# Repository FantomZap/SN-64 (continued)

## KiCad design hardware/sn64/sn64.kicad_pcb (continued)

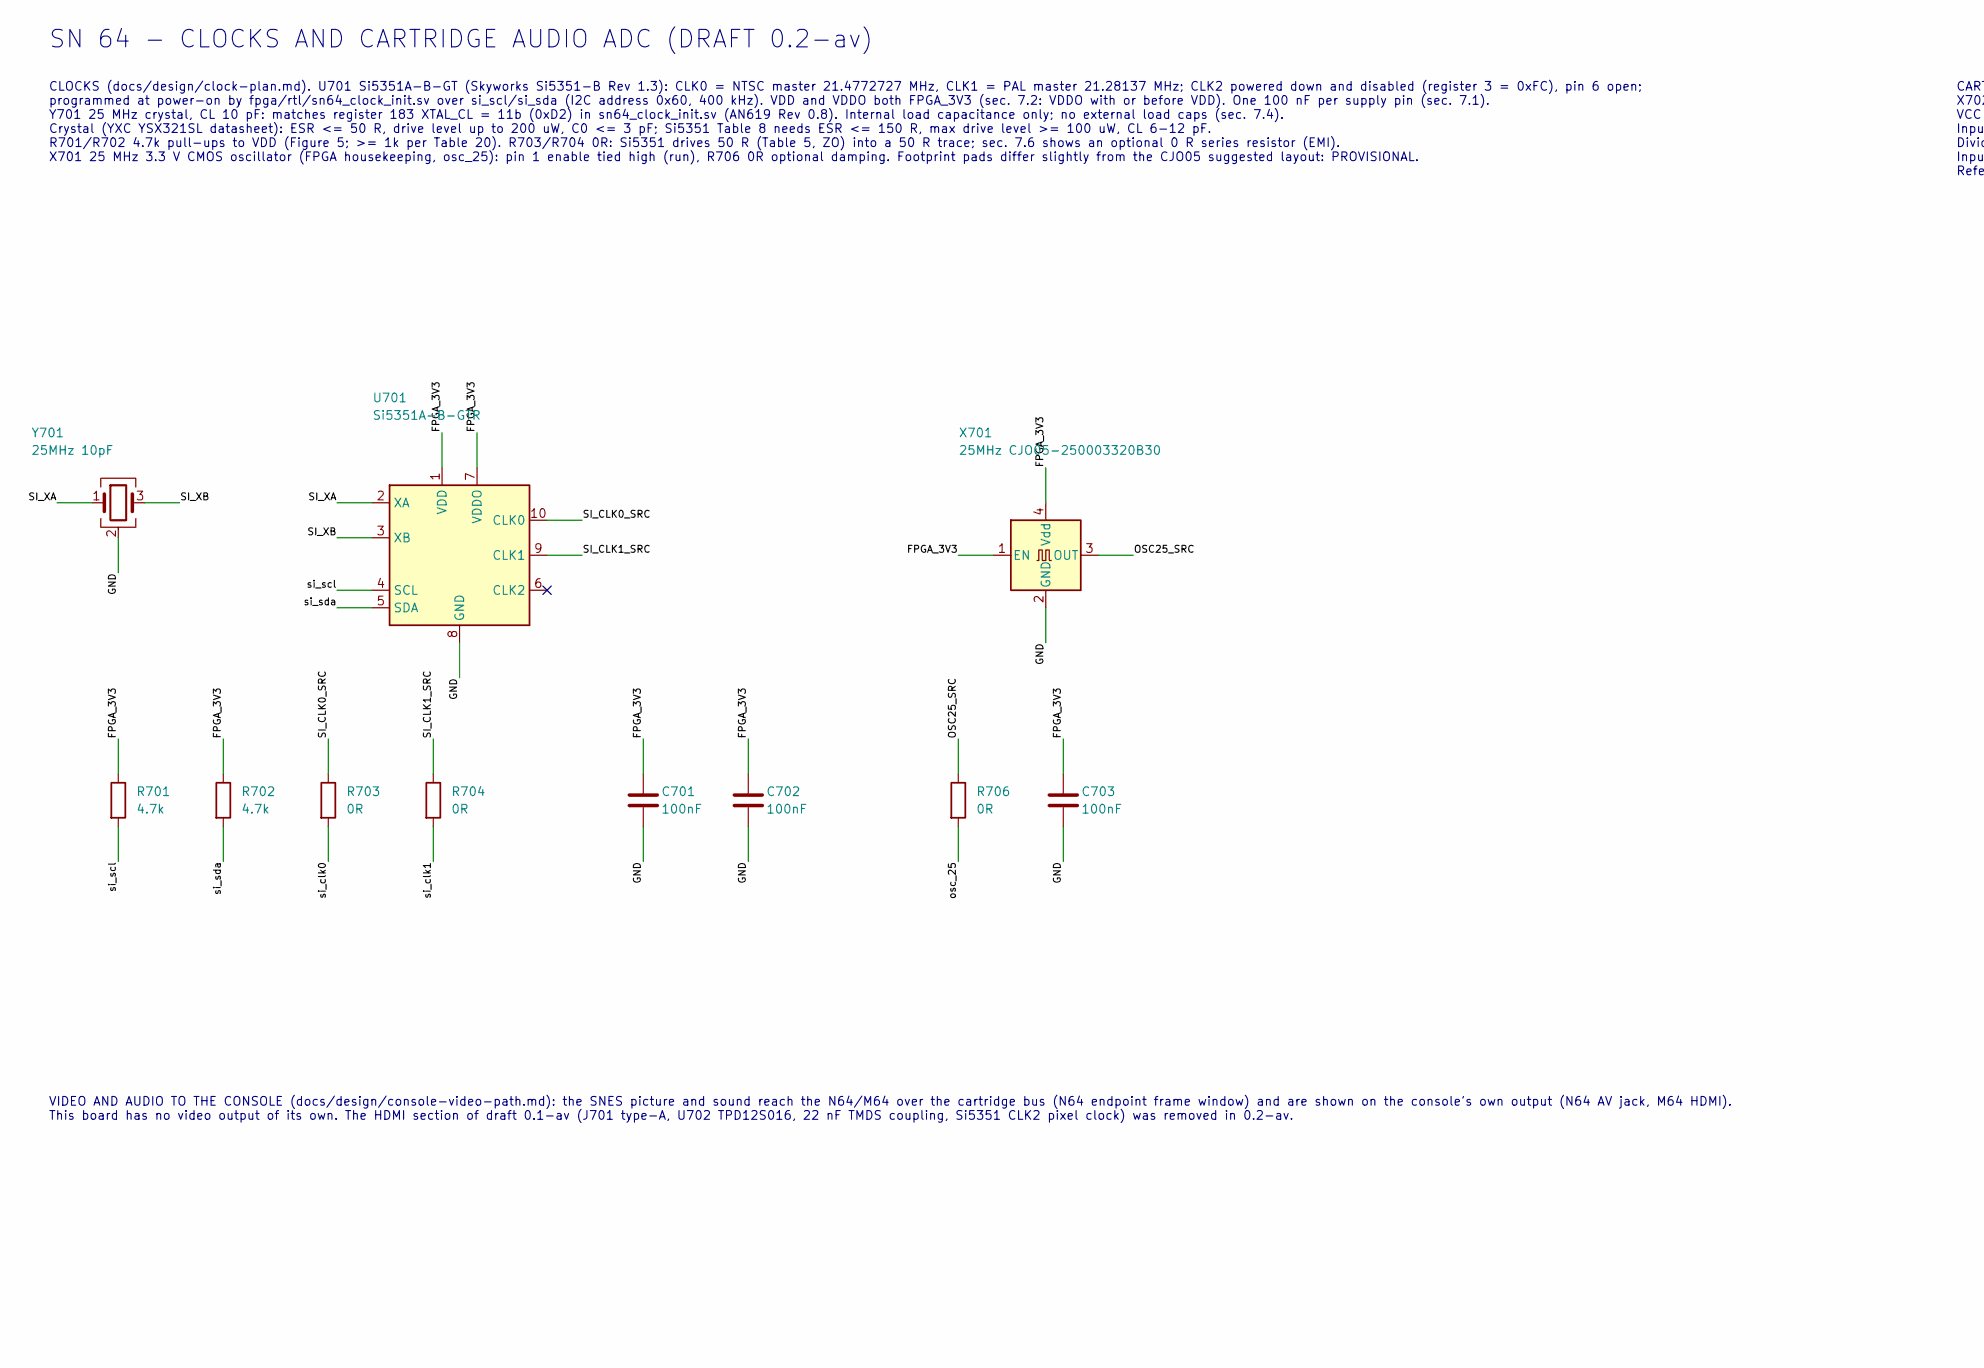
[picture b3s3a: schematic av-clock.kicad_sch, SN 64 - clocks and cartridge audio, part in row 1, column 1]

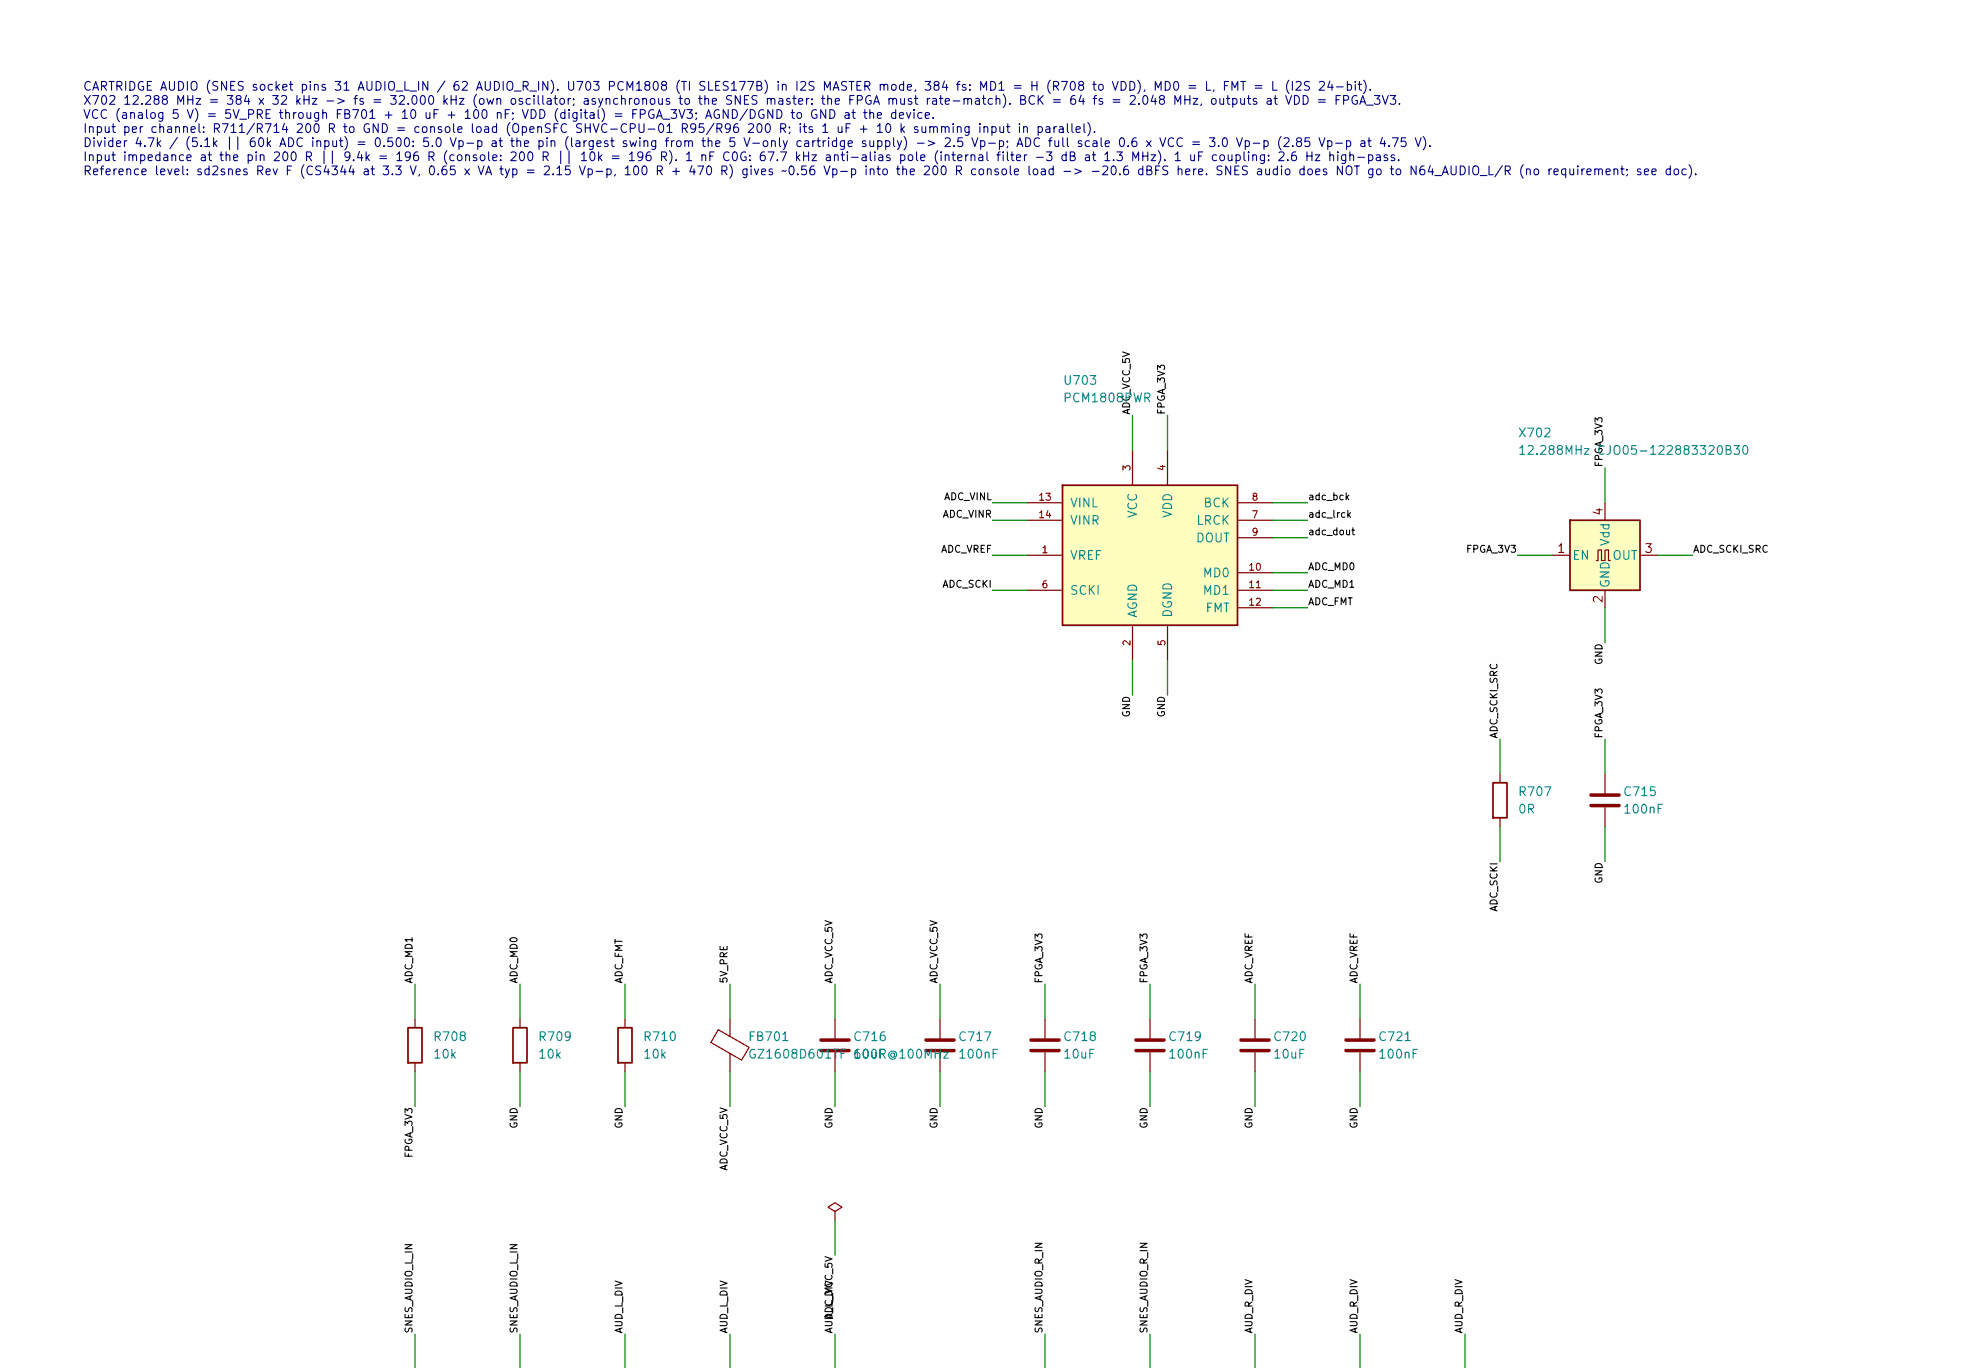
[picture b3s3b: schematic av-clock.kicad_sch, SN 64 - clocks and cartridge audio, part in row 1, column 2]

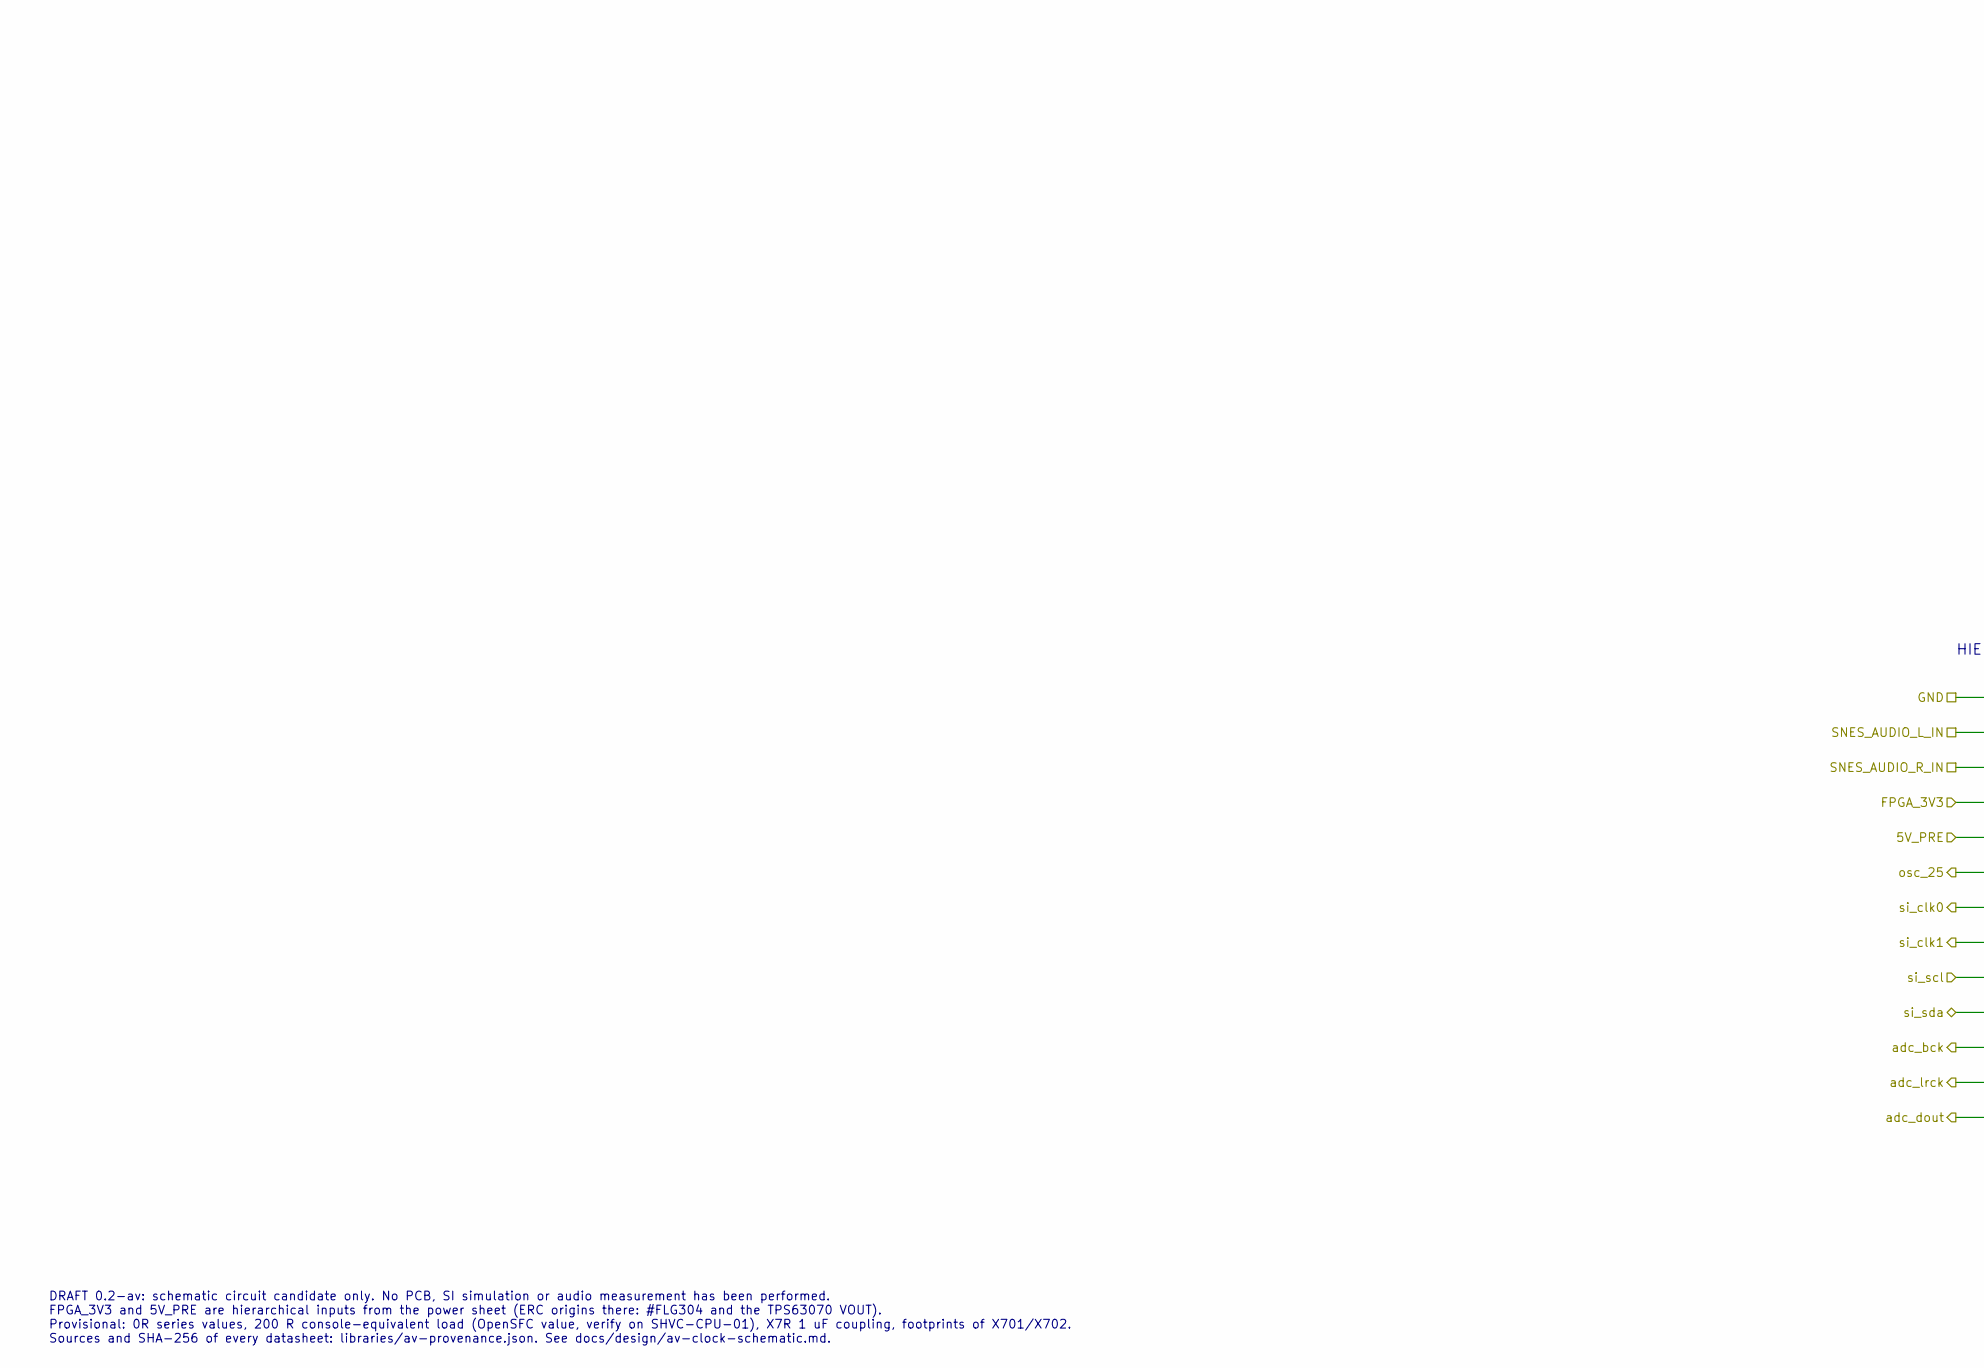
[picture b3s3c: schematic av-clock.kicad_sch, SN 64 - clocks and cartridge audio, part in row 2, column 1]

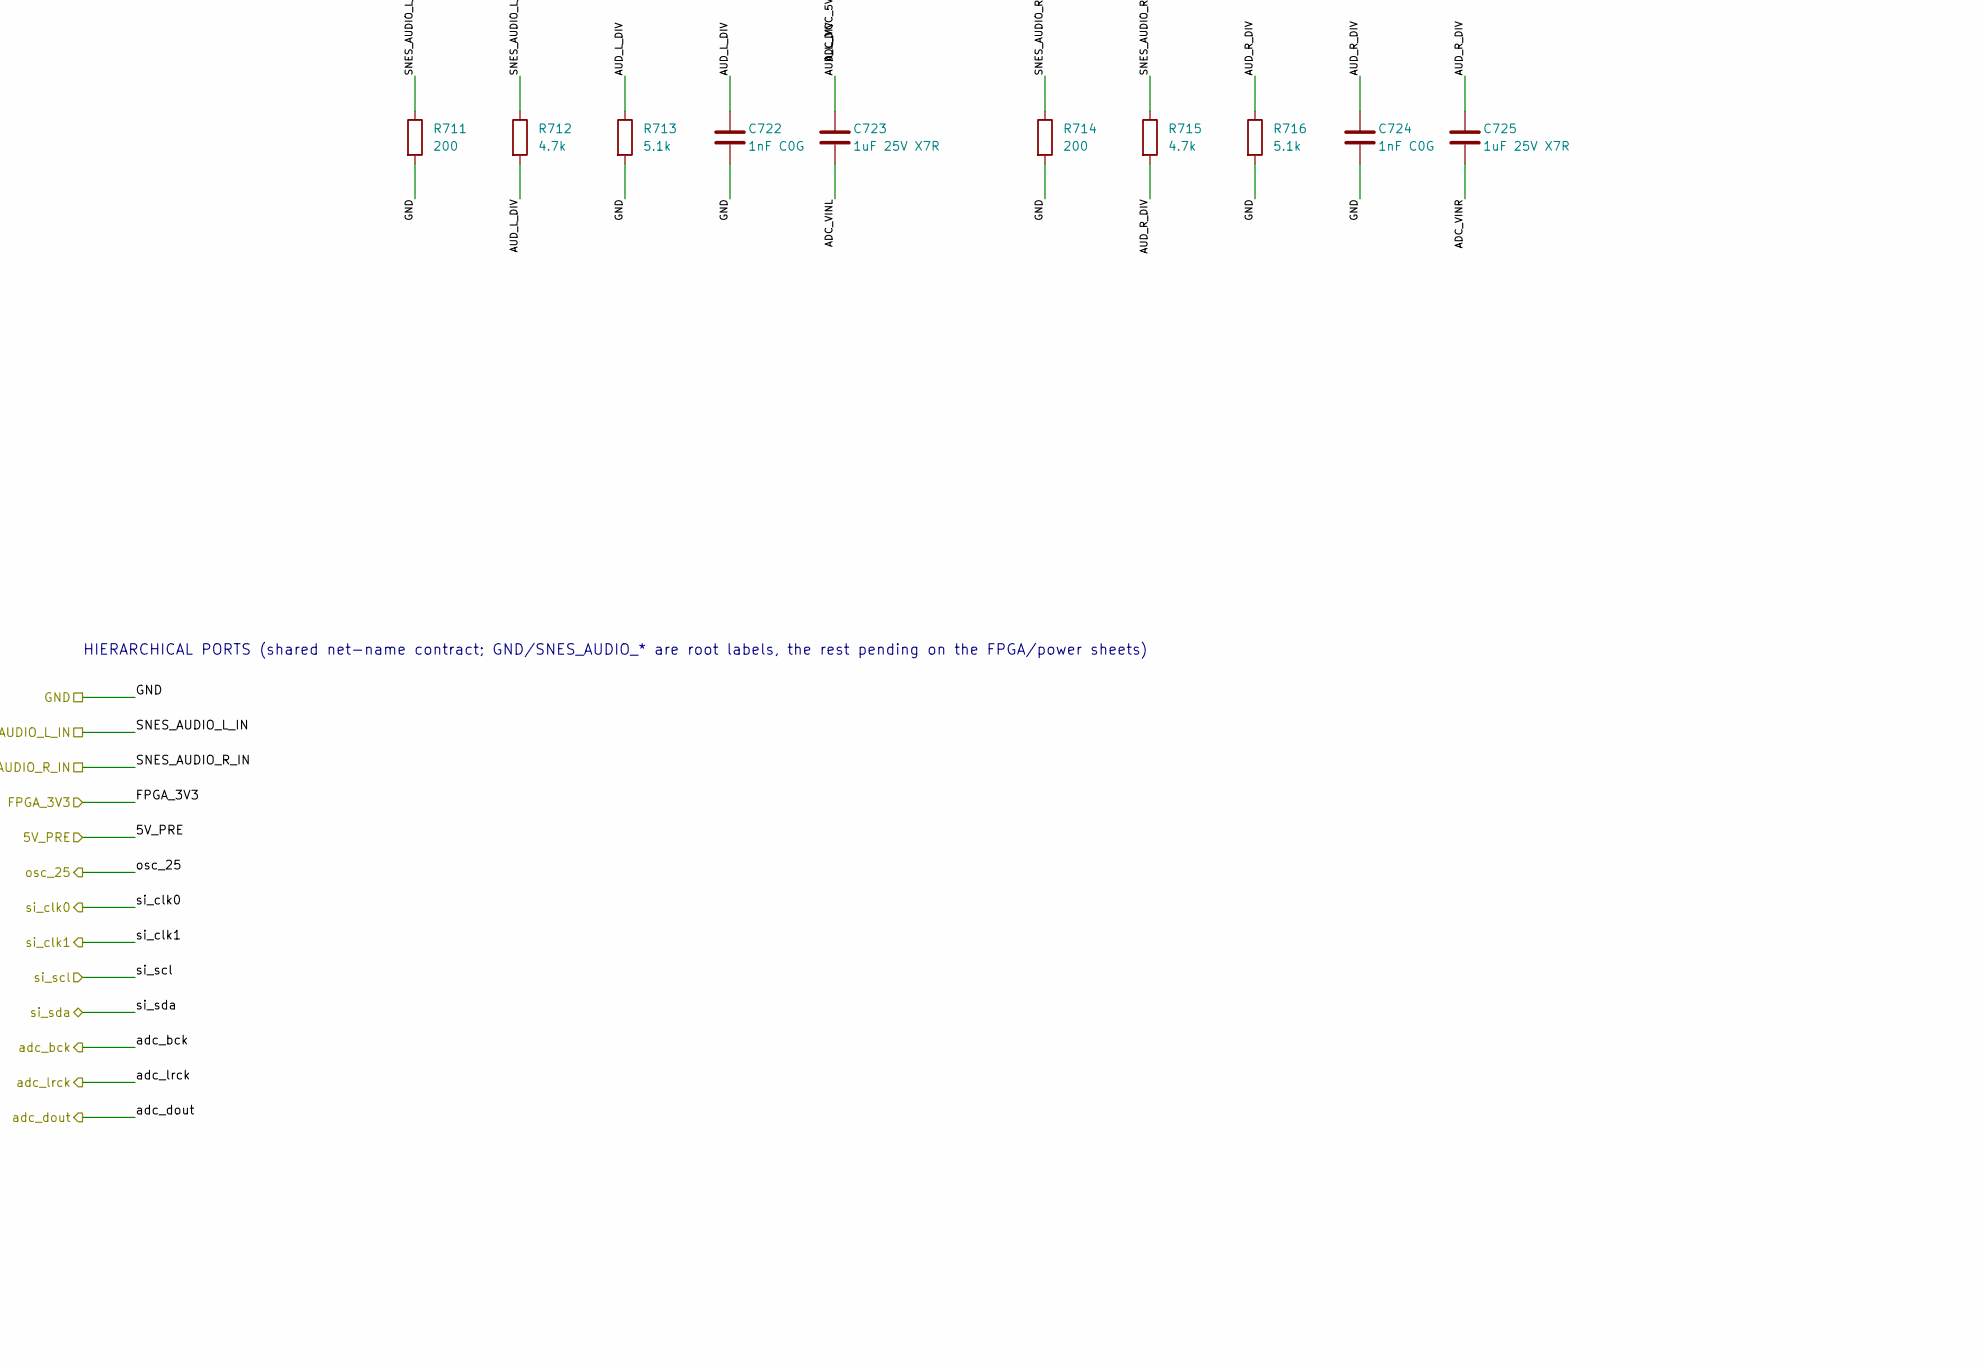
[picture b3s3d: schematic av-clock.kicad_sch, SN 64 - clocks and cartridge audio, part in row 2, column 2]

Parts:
C701, C702, C703, C715, C717, C719, C721: 100nF; C_0603_1608Metric
C716, C718, C720: 10uF; C_0805_2012Metric
C722, C724: 1nF C0G; C_0603_1608Metric
C723, C725: 1uF 25V X7R; C_0805_2012Metric
FB701: GZ1608D601TF 600R@100MHz; L_0603_1608Metric; MPN GZ1608D601TF; LCSC C1002
R701, R702, R712, R715: 4.7k; R_0603_1608Metric
R703, R704, R706, R707: 0R; R_0603_1608Metric
R708, R709, R710: 10k; R_0603_1608Metric
R711, R714: 200; R_0603_1608Metric
R713, R716: 5.1k; R_0603_1608Metric
U701: Si5351A-B-GTR; MSOP-10_3x3mm_P0.5mm; MPN Si5351A-B-GTR; LCSC C504891
U703: PCM1808PWR; TSSOP-14_4.4x5mm_P0.65mm; MPN PCM1808PWR; LCSC C55513
X701: 25MHz CJO05-250003320B30; Oscillator_SMD_Abracon_ASE-4Pin_3.2x2.5mm; MPN CJO05-250003320B30; LCSC C712741
X702: 12.288MHz CJO05-122883320B30; Oscillator_SMD_Abracon_ASE-4Pin_3.2x2.5mm; MPN CJO05-122883320B30; LCSC C712747
Y701: 25MHz 10pF; Crystal_SMD_3225-4Pin_3.2x2.5mm; MPN X322525MMB4SI; LCSC C70582

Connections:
/5V_PRE: FB701.1; also elsewhere on the board
/AV clock and cartridge audio/ADC_FMT: R710.1, U703.12 (FMT)
/AV clock and cartridge audio/ADC_MD0: R709.1, U703.10 (MD0)
/AV clock and cartridge audio/ADC_MD1: R708.1, U703.11 (MD1)
/AV clock and cartridge audio/ADC_SCKI: R707.2, U703.6 (SCKI)
/AV clock and cartridge audio/ADC_SCKI_SRC: R707.1, X702.3 (OUT)
/AV clock and cartridge audio/ADC_VCC_5V: C716.1, C717.1, FB701.2, U703.3 (VCC)
/AV clock and cartridge audio/ADC_VINL: C723.2, U703.13 (VINL)
/AV clock and cartridge audio/ADC_VINR: C725.2, U703.14 (VINR)
/AV clock and cartridge audio/ADC_VREF: C720.1, C721.1, U703.1 (VREF)
/AV clock and cartridge audio/AUD_L_DIV: C722.1, C723.1, R712.2, R713.1
/AV clock and cartridge audio/AUD_R_DIV: C724.1, C725.1, R715.2, R716.1
/AV clock and cartridge audio/OSC25_SRC: R706.1, X701.3 (OUT)
/AV clock and cartridge audio/SI_CLK0_SRC: R703.1, U701.10 (CLK0)
/AV clock and cartridge audio/SI_CLK1_SRC: R704.1, U701.9 (CLK1)
/AV clock and cartridge audio/SI_XA: U701.2 (XA), Y701.1
/AV clock and cartridge audio/SI_XB: U701.3 (XB), Y701.3
/FPGA_3V3: C701.1, C702.1, C703.1, C715.1, C718.1, C719.1, R701.1, R702.1, R708.2, U701.1 (VDD), U701.7 (VDDO), U703.4 (VDD), X701.1 (EN), X701.4 (Vdd), X702.1 (EN), X702.4 (Vdd); also elsewhere on the board
/GND: C701.2, C702.2, C703.2, C715.2, C716.2, C717.2, C718.2, C719.2, C720.2, C721.2, C722.2, C724.2, R709.2, R710.2, R711.2, R713.2, R714.2, R716.2, U701.8 (GND), U703.2 (AGND), U703.5 (DGND), X701.2 (GND), X702.2 (GND), Y701.2 (G), Y701.4 (G); also elsewhere on the board
/SNES_AUDIO_L_IN: R711.1, R712.1; also elsewhere on the board
/SNES_AUDIO_R_IN: R714.1, R715.1; also elsewhere on the board
/adc_bck: U703.8 (BCK); also elsewhere on the board
/adc_dout: U703.9 (DOUT); also elsewhere on the board
/adc_lrck: U703.7 (LRCK); also elsewhere on the board
/osc_25: R706.2; also elsewhere on the board
/si_clk0: R703.2; also elsewhere on the board
/si_clk1: R704.2; also elsewhere on the board
/si_scl: R701.2, U701.4 (SCL); also elsewhere on the board
/si_sda: R702.2, U701.5 (SDA); also elsewhere on the board

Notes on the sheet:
SN 64 - CLOCKS AND CARTRIDGE AUDIO ADC (DRAFT 0.2-av)
CLOCKS (docs/design/clock-plan.md). U701 Si5351A-B-GT (Skyworks Si5351-B Rev 1.3): CLK0 = NTSC master 21.4772727 MHz, CLK1 = PAL master 21.28137 MHz; CLK2 powered down and disabled (register 3 = 0xFC), pin 6 open; programmed at power-on by fpga/rtl/sn64_clock_init.sv over si_scl/si_sda (I2C address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
VIDEO AND AUDIO TO THE CONSOLE (docs/design/console-video-path.md): the SNES picture and sound reach the N64/M64 over the cartridge bus (N64 endpoint frame window) and are shown on the console's own output (N64 AV jack, M64 HDMI). This board has no video output of its own. The HDMI section of draft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
CARTRIDGE AUDIO (SNES socket pins 31 AUDIO_L_IN / 62 AUDIO_R_IN). U703 PCM1808 (TI SLES177B) in I2S MASTER mode, 384 fs: MD1 = H (R708 to VDD), MD0 = L, FMT = L (I2S 24-bit). X702 12.288 MHz = 384 x 32 kHz -> fs = 32.000 kHz (own oscillator; asynchronous to the SNES master: the FPGA must rate-match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
HIERARCHICAL PORTS (shared net-name contract; GND/SNES_AUDIO_* are root labels, the rest pending on the FPGA/power sheets)
DRAFT 0.2-av: schematic circuit candidate only. No PCB, SI simulation or audio measurement has been performed. FPGA_3V3 and 5V_PRE are hierarchical inputs from the power sheet (ERC origins there: #FLG304 and the TPS63070 VOUT). Provisional: 0R series values, 200 R console-equivalent load (OpenSFC v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

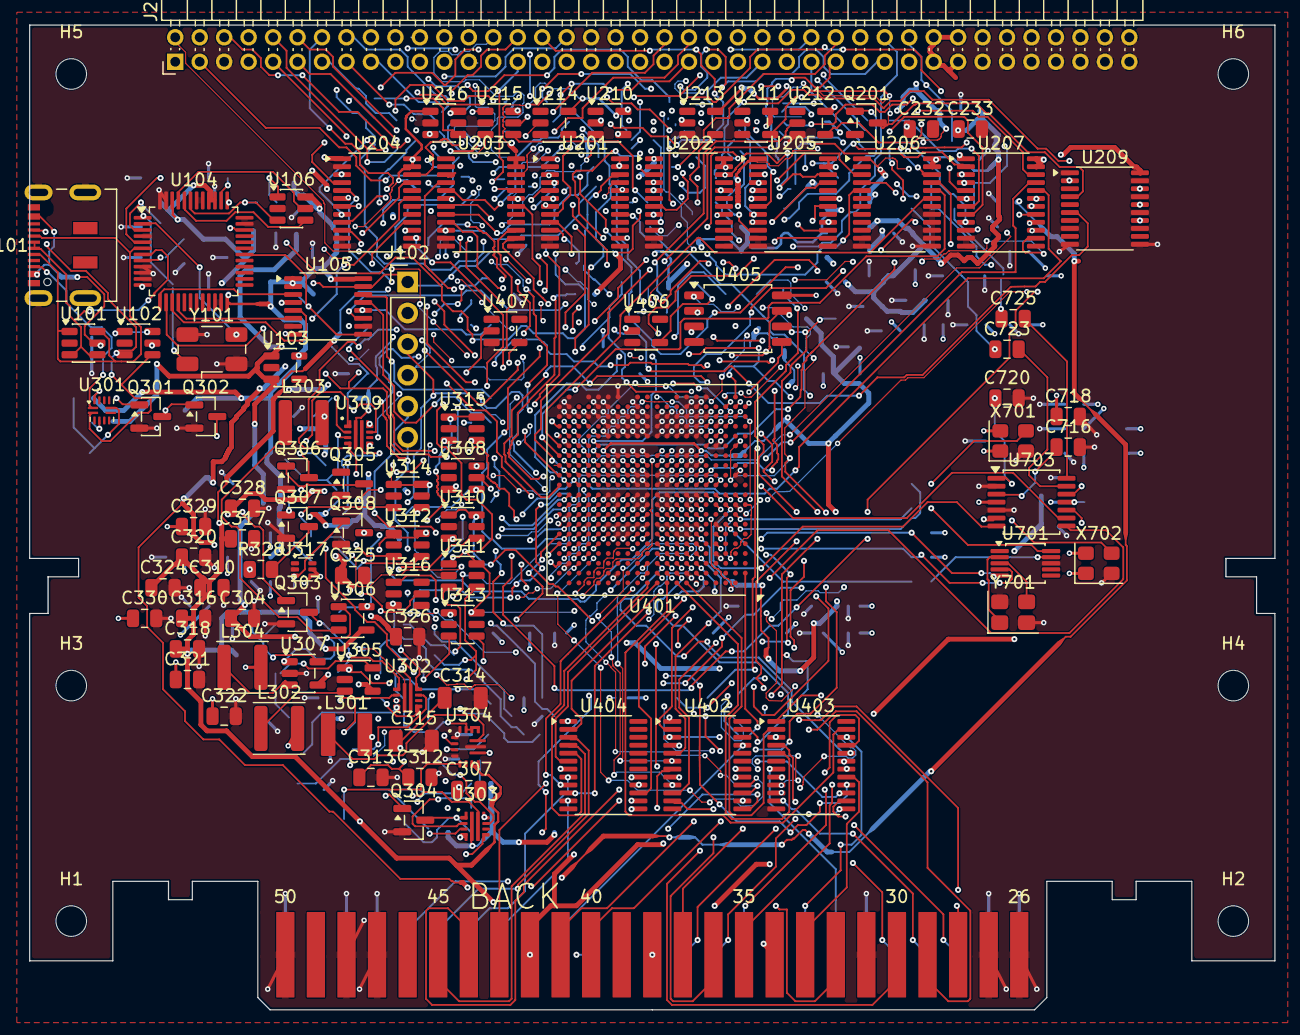
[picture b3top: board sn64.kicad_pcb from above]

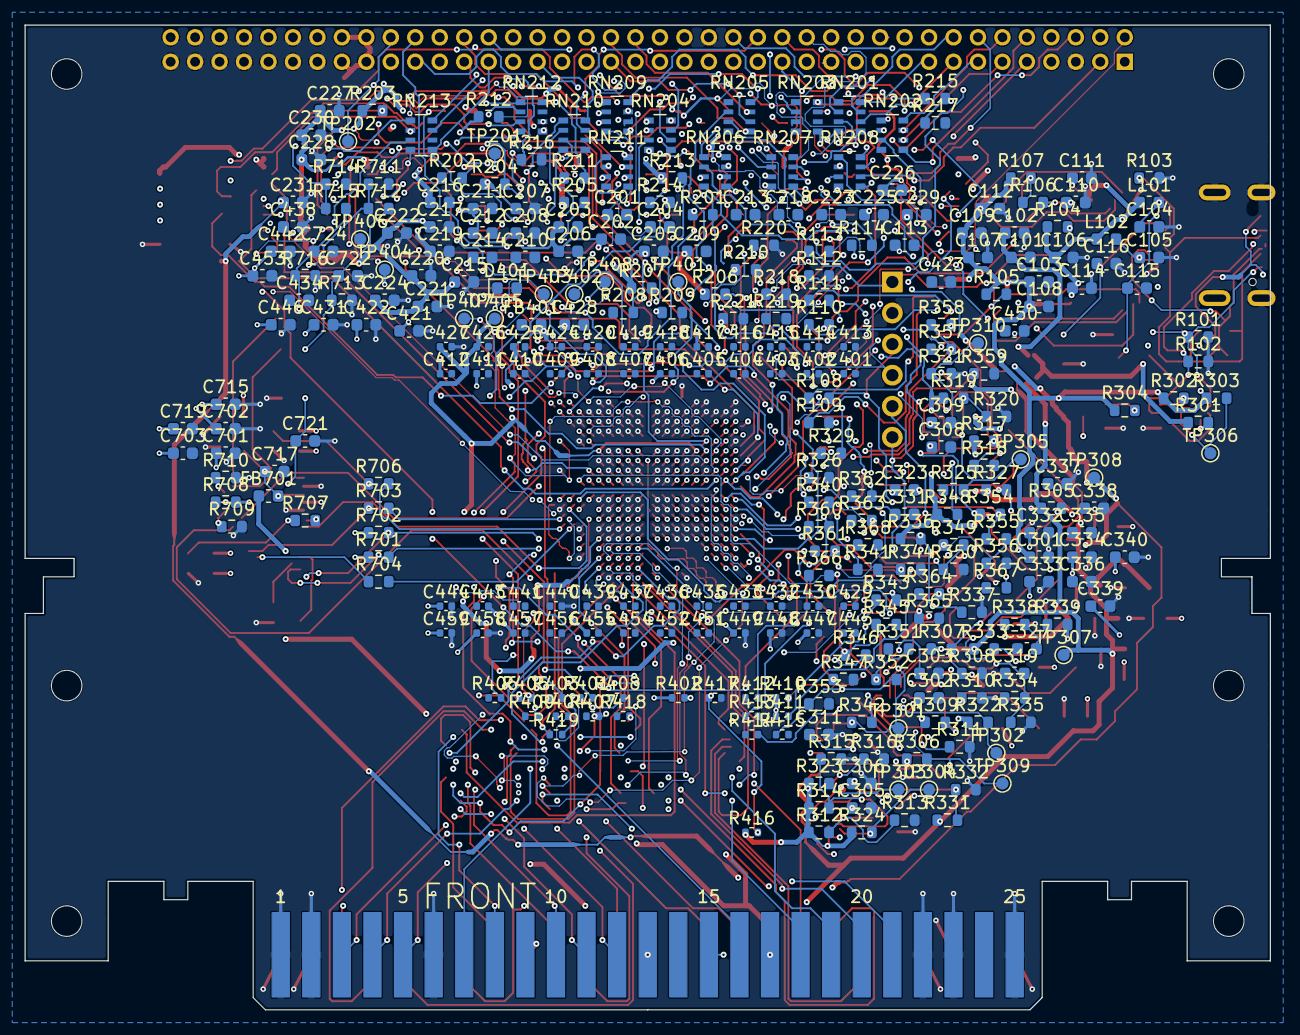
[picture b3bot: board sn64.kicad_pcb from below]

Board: 6 copper layers, 101.8 x 80.5 mm, 410 parts (309 on the bottom side), 378 nets.

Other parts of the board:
H1, H2, H3, H4, H5, H6: MountingHole_2.5mm

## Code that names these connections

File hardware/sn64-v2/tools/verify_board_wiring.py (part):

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            bad.append('%s (%s): reaches socket pins %s' % (port, signal, got))
        if b.net(ref, t['dir']) != b.port_net('data_dir') or b.net(ref, t['oe']) != b.port_net('data_oe_n'):
            bad.append('%s: direction on %s, enable on %s' % (port, b.net(ref, t['dir']), b.net(ref, t['oe'])))
    check('D0-D7 reach their socket pins through one byte whose direction is data_dir and whose enable is data_oe_n', not bad, '; '.join(bad[:6]))
    pulls = [b.two_pin(b.port_net(p), 'R') for p in ('ctl_oe_n', 'cic_oe_n', 'data_oe_n', 'sense_oe_n')]
    check('the four level-shifter enables are pulled to 3.3 V, so every byte is off until the FPGA drives them',
          all(any(o == v33 for _, _, o in pl) for pl in pulls), str(pulls))
    check('data_dir is pulled low, so the data byte points away from the cartridge until the FPGA drives it',
          any(o == gnd for _, _, o in b.two_pin(b.port_net('data_dir'), 'R')), str(b.two_pin(b.port_net('data_dir'), 'R')))

    # 4. Cartridge inputs: a channel that points B to A, switched by sense_oe_n.
    bad = []
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        if b.net(ref, t['dir']) != gnd or b.net(ref, t['oe']) != b.port_net('sense_oe_n'):
            bad.append('%s: direction on %s (should be ground), enable on %s (should be the net of sense_oe_n)' % (
                port, b.net(ref, t['dir']), b.net(ref, t['oe'])))
    check('%d cartridge inputs come from their own socket pin through a channel that points to the FPGA and is switched by sense_oe_n' % len(SNES_IN),
          not bad, '; '.join(bad[:6]))

    # 4b. Rules of the level shifter's data sheet (TI SCAS416Q). Section 10: /OE is to be high until
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          and len(sw) == 1 and b.net(sw[0], '6') == cart5 and cart5 not in (gnd, v33, None),
          'socket +5 V net %s, switch %s output %s' % (cart5, sw, b.net(sw[0], '6') if sw else None))
    check('the cartridge switch is off until the FPGA turns it on (enable pulled low, driven by cart_5v_enable)',
          len(sw) == 1 and b.net(sw[0], '3') == b.port_net('cart_5v_enable') and any(o == gnd for _, _, o in b.two_pin(b.net(sw[0], '3'), 'R')),
          str(b.two_pin(b.net(sw[0], '3'), 'R')) if sw else '')

    # 8. N64 edge: ports straight on their fingers.
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            bad.append('flash clock does not reach the CCLK ball through a series resistor')
        if b.net(f, FLASH['vcc']) != v33 or b.net(f, FLASH['gnd']) != gnd:
            bad.append('flash supply pins')
        for port, pin in (('flash_cs_n', 'cs'), ('flash_dq[0]', 'd0'), ('flash_dq[1]', 'd1'), ('flash_dq[2]', 'd2'), ('flash_dq[3]', 'd3')):
            if b.port_net(port) != b.net(f, FLASH[pin]):
                bad.append('port %s is not on flash pin %s' % (port, pin))
    for name, rail in (('cfg0', gnd), ('cfg1', v33), ('cfg2', gnd), ('done', v33), ('initn', v33), ('programn', v33)):
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    ('the supply converter address pin tied to ground', lambda d, l: d['components']['U6']['pads'].__setitem__('11', 'GND')),
    ('the cartridge supply divider on the wrong converter input', lambda d, l: swap(d, ('U6', '2'), ('U6', '3'))),
    ('level shifter B side on 3.3 V', lambda d, l: d['components']['U203']['pads'].__setitem__('7', 'FPGA_3V3')),
    ('two FPGA ports exchanged in the constraints', lambda d, l: l.update({'cart_rd_n': l['cart_wr_n'], 'cart_wr_n': l['cart_rd_n']})),
    ('N64 address/data lines swapped on the edge', lambda d, l: swap(d, ('J1', '28'), ('J1', '29'))),
    ('N64 edge rows exchanged (pins 1-25 with 26-50)', lambda d, l: [swap(d, ('J1', str(i)), ('J1', str(i + 25))) for i in range(1, 26)]),
    ('flash data lines swapped', lambda d, l: swap(d, ('U2', '2'), ('U2', '5'))),
    ('configuration mode pin pulled the wrong way', lambda d, l: [d['components'][r]['pads'].update({p: 'GND' if n == 'FPGA_3V3' else n for p, n in d['components'][r]['pads'].items()})
                                                                  for r in ('R6',)]),
    ('USB data lines swapped at the connector', lambda d, l: [swap(d, ('J101', 'A6'), ('J101', 'A7')), swap(d, ('J101', 'B6'), ('J101', 'B7'))]),
    ('JTAG clock and mode select swapped at the loader chip', lambda d, l: swap(d, ('U13', '7'), ('U13', '8'))),
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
